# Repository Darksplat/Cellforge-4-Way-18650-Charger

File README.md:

# CellForge – 4 Way 18650 Charger & Analytics Platform

CellForge is an open hardware and software project for testing, analysing, and cataloguing 18650 lithium-ion cells.

It is inspired by Brett Watt’s original ASCD Nano charger and extends the concept with modern hardware, Wi-Fi connectivity, and a web-based analytics platform.

This repository contains **firmware, hardware, documentation, and web platform components** required to build and operate a connected 4-bay charger.

---

## Project Components

### Hardware
- 4-slot 18650 charger / discharger
- TP5100 charge controllers per slot
- Dual ADS1115 (16-bit I²C ADCs)
  - Battery voltage sensing
  - Load / discharge voltage sensing
- DS18B20 temperature sensors
- Active cooling with PWM fan control
- 3.3 V logic throughout (ESP32-safe)

### Firmware
- Target: **Arduino Nano ESP32 (ESP32-S3)**
- Wi-Fi connectivity
- Server heartbeat (PING) protocol
- RSSI (signal strength) reporting
- Internal resistance measurement
- Capacity and energy calculation
- Modular PlatformIO-based build

### Web Platform
- PHP + MySQL backend
- User authentication
- Charger registration and claiming
- Live charger connectivity status
- Signal strength visualisation
- Cell inventory
- Run ingestion (start, IR, complete, error)
- Cron-based offline detection

### Data
- Cell metadata (barcode-centric)
- Internal resistance results
- Capacity (mAh) and energy (Wh)
- Charger telemetry (presence, RSSI)

---

## Current Status

- Firmware: **Stable, Wi-Fi enabled**
- Connectivity: **Server-authoritative heartbeat**
- Telemetry: **RSSI reporting live**
- Offline detection: **Cron-enforced**
- UI: **Live status, signal bars, local time rendering**

---

## Repository Structure (high-level)

---

## Design Principles

- Server decides truth (presence, offline state)
- Firmware reports facts, not assumptions
- Browser renders user-local time
- Hardware remains Brett-compatible where practical
- Electrical safety first (3.3 V logic, no mixed-voltage traps)

---

## Licensing

Original ASCD Nano work:
- © Brett Watt
- Creative Commons BY-NC-SA 3.0

CellForge modifications:
- © Jeremy Younger
- Released under the same license unless otherwise stated

---

## Disclaimer

This project involves lithium-ion cells.
Improper use can result in fire, injury, or property damage.

You are responsible for ensuring safe construction, operation, and supervision.

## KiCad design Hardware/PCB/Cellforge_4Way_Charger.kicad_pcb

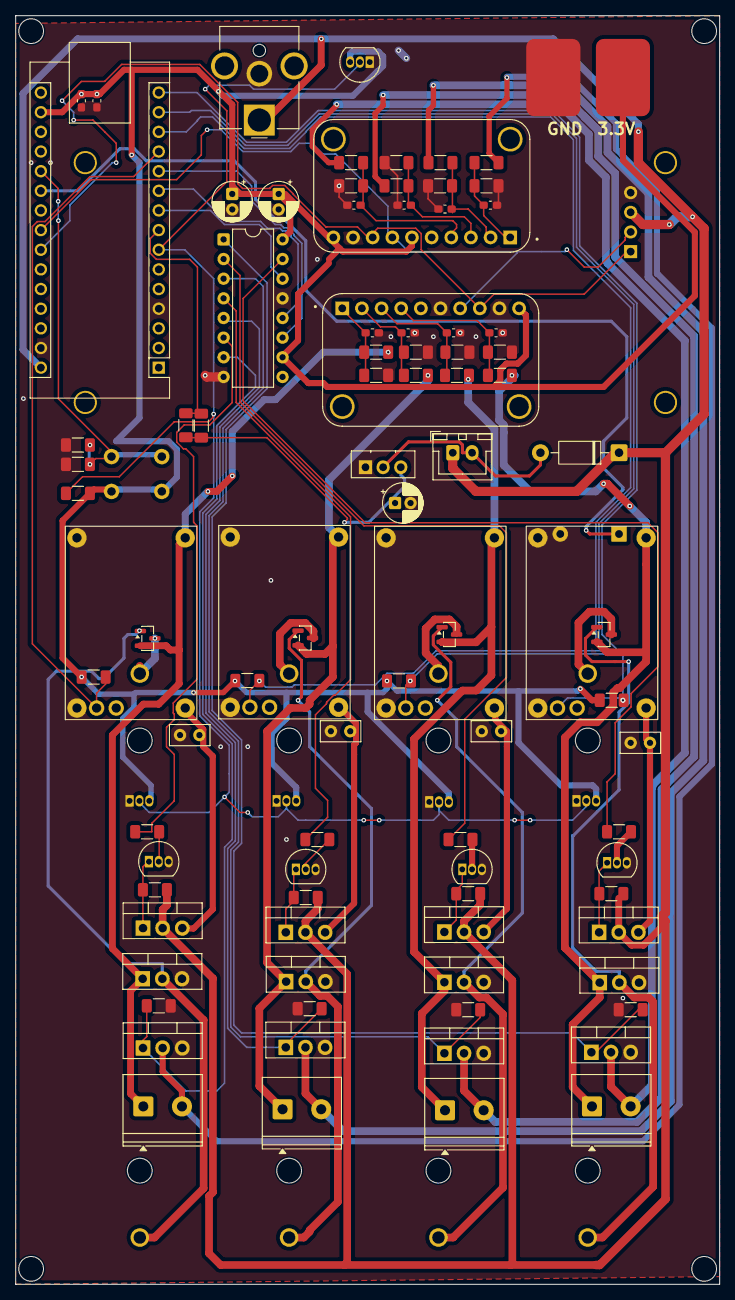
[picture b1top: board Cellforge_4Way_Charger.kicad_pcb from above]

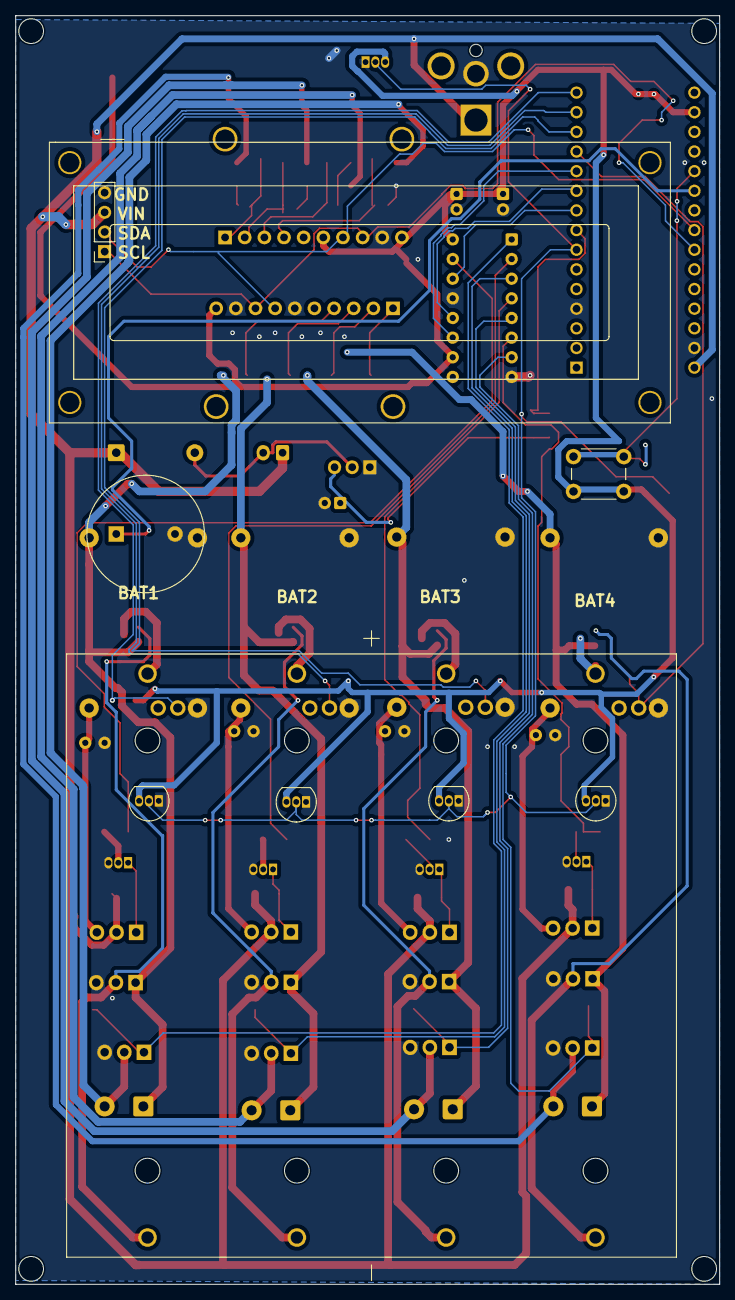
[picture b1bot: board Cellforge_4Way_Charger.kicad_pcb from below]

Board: 2 copper layers, 91.0 x 164.0 mm, 100 parts (8 on the bottom side), 62 nets.

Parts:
A1: Arduino_Nano_ESP32; Arduino_Nano
BT1: BK-18650-PC8; BAT_BK-18650-PC8
BZ1: Buzzer; Buzzer_15x7.5RM7.6
C1, C2, C11: 100uF; CP_Radial_D5.0mm_P2.00mm
C3, C4, C5, C6, C7, C8, C9, C10, C13: 100nF; C_0603_1608Metric_Pad1.08x0.95mm_HandSolder
C12, C16, C17, C18: C; C_Disc_D5.0mm_W2.5mm_P2.50mm
C14: 10nF; C_0603_1608Metric_Pad1.08x0.95mm_HandSolder
D1: 1N4007; D_DO-41_SOD81_P10.16mm_Horizontal
J1: Jack-DC; BarrelJack_CUI_PJ-063AH_Horizontal_CircularHoles
J2: Conn_01x02_MountingPin; JST_XH_B2B-XH-A_1x02_P2.50mm_Vertical
J3, J4, J6, J7: Screw_Terminal_01x02; TerminalBlock_Phoenix_PT-1,5-2-5.0-H_1x02_P5.00mm_Horizontal
J5: Conn_01x04_Socket; PinSocket_1x04_P2.54mm_Vertical
J8: Conn_01x02_Pin; PADS
Q1: BD139; TO-126-3_Vertical
Q2, Q3, Q8, Q23: AO3401A; SOT-23
Q6, Q7, Q9, Q10: BC547; TO-92_Inline
Q11, Q12, Q13, Q14, Q15, Q16, Q17, Q19: IRLZ44N; TO-220-3_Vertical
Q18, Q20, Q21, Q22: FQP27P06; TO-220-3_Vertical
R1, R21, R32, R36: 4.7K; R_1206_3216Metric_Pad1.30x1.75mm_HandSolder
R2, R3, R20, R35, R43, R50: 10K; R_1206_3216Metric_Pad1.30x1.75mm_HandSolder
R4, R5, R6, R7, R8, R9, R10, R11, R12, R13, R14, R15, R16, R17, R18, R19: 100K; R_1206_3216Metric_Pad1.30x1.75mm_HandSolder
R22: 1K; R_1206_3216Metric_Pad1.30x1.75mm_HandSolder
R23: 1k; R_1206_3216Metric_Pad1.30x1.75mm_HandSolder
R33, R34, R37, R38, R39, R40, R41, R42, R44: 470R; R_1206_3216Metric_Pad1.30x1.75mm_HandSolder
SW1: SW_Push; SW_PUSH_6mm
TP5100_Module1, TP5100_Module2, TP5100_Module3, TP5100_Module4: Untitled
U1, U2, U3, U4, U7: DS18B20; TO-92_Inline
U5: 74HC595; DIP-16_W7.62mm
U6, U9: ZC261500; MODULE_ZC261500

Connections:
+3.3V: A1.17 (3V3), C1.1, C2.1, C13.1, C14.1, J8.1, R1.1, R20.1, R35.1, R43.1, R50.1, SW1.2, U1.3 (V_{DD}), U2.3 (V_{DD}), U3.3 (V_{DD}), U4.3 (V_{DD}), U5.10 (~SRCLR), U5.16 (VCC), U6.6 (ADDR), U6.10 (VDD), U7.3 (V_{DD}), U9.10 (VDD)
+BAT1: J3.1, Q8.2 (S), Q15.1 (G), R4.1, TP5100_Module1.3 (BAT+)
+BAT2: J7.1, Q17.1 (G), Q23.2 (S), R12.1, TP5100_Module2.3 (BAT+)
+BAT3: J4.1, Q2.2 (S), Q12.1 (G), R18.1, TP5100_Module3.3 (BAT+)
+BAT4: J6.1, Q3.2 (S), Q19.1 (G), R16.1, TP5100_Module4.3 (BAT+)
-BAT1: BT1.4-, Q8.1 (G), Q15.2 (D)
-BAT2: BT1.3-, Q17.2 (D), Q23.1 (G)
-BAT3: BT1.2-, Q2.1 (G), Q12.2 (D)
-BAT4: BT1.1-, Q3.1 (G), Q19.2 (D)
BTN: A1.20 (A1), R2.2, R3.1, SW1.1
BUZZ: A1.21 (A2), BZ1.1 (+)
CD1: A1.15 (D12/CIPO), R20.2, TP5100_Module1.5 (CHRG)
CD2: A1.14 (D11/COPI), R43.2, TP5100_Module2.5 (CHRG)
CD3: A1.13 (D10/CS), R50.2, TP5100_Module3.5 (CHRG)
CD4: A1.12 (D9), R35.2, TP5100_Module4.5 (CHRG)
CEFT2: R42.2, U5.2 (QC)
CEFT3: R44.2, U5.4 (QE)
CEFT4: R34.2, U5.6 (QG)
CFET1: R38.2, U5.15 (QA)
DFET1: Q13.1 (G), R21.1, U5.1 (QB)
DFET2: Q16.1 (G), R36.1, U5.3 (QD)
DFET3: Q11.1 (G), R32.1, U5.5 (QF)
DFET4: Q14.1 (G), R33.1, U5.7 (QH)
DS: A1.9 (D6), U5.14 (SER)
FAN: A1.8 (D5), R22.1, R23.1
GND: A1.4 (GND), A1.29 (GND), BZ1.2 (-), C1.2, C2.2, C3.2, C4.2, C5.2, C6.2, C7.2, C8.2, C9.2, C10.2, C11.2, C12.2, C13.2, C14.2, C16.2, C17.2, C18.2, J1.2, J5.4, J8.2, Q1.1 (E), Q6.3 (E), Q7.3 (E), Q9.3 (E), Q10.3 (E), Q11.3 (S), Q12.3 (S), Q13.3 (S), Q14.3 (S), Q15.3 (S), Q16.3 (S), Q17.3 (S), Q19.3 (S), R2.1, R3.2, R6.2, R9.2, R11.2, R13.2, R14.2, R15.2, R17.2, R19.2, R21.2, R32.2, R33.2, R36.2, TP5100_Module1.2 (IN-), TP5100_Module1.4 (BAT-), TP5100_Module2.2 (IN-), TP5100_Module2.4 (BAT-), TP5100_Module3.2 (IN-), TP5100_Module3.4 (BAT-), TP5100_Module4.2 (IN-), TP5100_Module4.4 (BAT-), U1.1 (GND), U2.1 (GND), U3.1 (GND), U4.1 (GND), U5.8 (GND), U5.13 (~OE), U6.9 (GND), U7.1 (GND), U9.6 (ADDR), U9.9 (GND)
unnamed: D1.2 (A), J2.2, Q1.2 (C)
unnamed: C11.1, Q1.3 (B), R22.2, R23.2
unnamed: BT1.2+, Q2.3 (D)
unnamed: BT1.1+, Q3.3 (D)
unnamed: Q6.2 (B), R44.1
unnamed: Q7.2 (B), R38.1
unnamed: BT1.4+, Q8.3 (D)
unnamed: Q9.2 (B), R42.1
unnamed: Q10.2 (B), R34.1
unnamed: Q10.1 (C), Q21.1 (G), R40.2
unnamed: Q7.1 (C), Q18.1 (G), R39.2
unnamed: C12.1, Q18.3 (S), TP5100_Module1.1 (IN+)
unnamed: Q6.1 (C), Q20.1 (G), R37.2
unnamed: C17.1, Q20.3 (S), TP5100_Module3.1 (IN+)
unnamed: C18.1, Q21.3 (S), TP5100_Module4.1 (IN+)
unnamed: Q9.1 (C), Q22.1 (G), R41.1
unnamed: C16.1, Q22.3 (S), TP5100_Module2.1 (IN+)
unnamed: BT1.3+, Q23.3 (D)
unnamed: C4.1, R8.2, R9.1, U6.4 (A0)
unnamed: C6.1, R10.2, R11.1, U6.3 (A1)
unnamed: C8.1, R7.2, R15.1, U6.2 (A2)
unnamed: C7.1, R5.2, R6.1, U6.1 (A3)
unnamed: C3.1, R4.2, R14.1, U9.4 (A0)
unnamed: C5.1, R12.2, R13.1, U9.3 (A1)
unnamed: C10.1, R18.2, R19.1, U9.2 (A2)
unnamed: C9.1, R16.2, R17.1, U9.1 (A3)
RV1: J3.2, Q13.2 (D), R8.1
RV2: J7.2, Q16.2 (D), R10.1
RV3: J4.2, Q11.2 (D), R7.1
RV4: J6.2, Q14.2 (D), R5.1
SCL: A1.24 (SCL/A5), J5.1, U6.8 (SCL), U9.8 (SCL)
SDA: A1.23 (SDA/A4), J5.2, U6.7 (SDA), U9.7 (SDA)
SH/CP: A1.11 (D8), U5.11 (SRCLK)
ST/CP: A1.10 (D7), U5.12 (RCLK)
TMP: A1.7 (D4), R1.2, U1.2 (DQ), U2.2 (DQ), U3.2 (DQ), U4.2 (DQ), U7.2 (DQ)
VIn: A1.30 (VIN), D1.1 (K), J1.1, J2.1, J5.3, Q18.2 (D), Q20.2 (D), Q21.2 (D), Q22.2 (D), R37.1, R39.1, R40.1, R41.2

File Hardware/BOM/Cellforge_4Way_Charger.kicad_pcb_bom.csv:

Designator,Quantity,Value,Footprint,Package,MPN,DNP,Mount_Type,Description,MF,MAXIMUM_PACKAGE_HEIGHT,Price,Check_prices,STANDARD,PARTREV,SnapEDA_Link,MP,Description_1,Availability,MANUFACTURER,Sim.Device,Sim.Pins
A1,1,Arduino_Nano_ESP32,Arduino_Nano,,,,tht,"Arduino Nano board based on the ESP32-S3 with a dual-core 240 MHz processor, 384 kB ROM, 512 kB SRAM. Operates at 3.3V, with 5V USB-C® input and 6-21V VIN. Features Wi-Fi®, Bluetooth® LE, digital and analog pins, and supports SPI, I2C, UART, I2S, and CAN.",,,,,,,,,,,,,
BT1,1,BK-18650-PC8,BAT_BK-18650-PC8,None,,,tht,,MPD,21.54 mm,None,https://www.snapeda.com/parts/BK-18650-PC8/MPD/view-part/?ref=eda,Manufacturer Recommendations,L,https://www.snapeda.com/parts/BK-18650-PC8/MPD/view-part/?ref=snap,BK-18650-PC8,Battery Holder (Open) 18650 4 Cell PC Pin,In Stock,MPD,,
BZ1,1,Buzzer,Buzzer_15x7.5RM7.6,,,,tht,"Buzzer, polarized",,,,,,,,,,,,,
"C1, C11, C2",3,100uF,CP_Radial_D5.0mm_P2.00mm,,,,tht,Polarized capacitor,,,,,,,,,,,,,
"C10, C13, C3, C4, C5, C6, C7, C8, C9",9,100nF,C_0603_1608Metric_Pad1.08x0.95mm_HandSolder,,,,smt,Unpolarized capacitor,,,,,,,,,,,,,
"C12, C16, C17, C18",4,C,C_Disc_D5.0mm_W2.5mm_P2.50mm,,,,tht,Unpolarized capacitor,,,,,,,,,,,,,
C14,1,10nF,C_0603_1608Metric_Pad1.08x0.95mm_HandSolder,,,,smt,Unpolarized capacitor,,,,,,,,,,,,,
D1,1,1N4007,D_DO-41_SOD81_P10.16mm_Horizontal,,,,tht,"1000V 1A General Purpose Rectifier Diode, DO-41",,,,,,,,,,,,D,1=K 2=A
J1,1,Jack-DC,BarrelJack_CUI_PJ-063AH_Horizontal_CircularHoles,,,,tht,DC Barrel Jack,,,,,,,,,,,,,
J2,1,Conn_01x02_MountingPin,JST_XH_B2B-XH-A_1x02_P2.50mm_Vertical,,,,tht,"Generic connectable mounting pin connector, single row, 01x02, script generated (kicad-library-utils/schlib/autogen/connector/)",,,,,,,,,,,,,
"J3, J4, J6, J7",4,Screw_Terminal_01x02,"TerminalBlock_Phoenix_PT-1,5-2-5.0-H_1x02_P5.00mm_Horizontal",,,,tht,"Generic screw terminal, single row, 01x02, script generated (kicad-library-utils/schlib/autogen/connector/)",,,,,,,,,,,,,
J5,1,Conn_01x04_Socket,PinSocket_1x04_P2.54mm_Vertical,,,,tht,"Generic connector, single row, 01x04, script generated",,,,,,,,,,,,,
J8,1,Conn_01x02_Pin,PADS,,,,smt,"Generic connector, single row, 01x02, script generated",,,,,,,,,,,,,
Q1,1,BD139,TO-126-3_Vertical,,,,tht,"1.5A Ic, 80V Vce, Low Voltage Transistor, TO-126",,,,,,,,,,,,,
"Q10, Q6, Q7, Q9",4,BC547,TO-92_Inline,,,,tht,"0.1A Ic, 45V Vce, Small Signal NPN Transistor, TO-92",,,,,,,,,,,,,
"Q11, Q12, Q13, Q14, Q15, Q16, Q17, Q19",8,IRLZ44N,TO-220-3_Vertical,,,,tht,"47A Id, 55V Vds, 22mOhm Rds Single N-Channel HEXFET Power MOSFET, TO-220AB",,,,,,,,,,,,,
"Q18, Q20, Q21, Q22",4,FQP27P06,TO-220-3_Vertical,,,,tht,"-27A Id, -60V Vds, QFET P-Channel MOSFET, TO-220",,,,,,,,,,,,,
"Q2, Q23, Q3, Q8",4,AO3401A,SOT-23,,,,smt,"-4.0A Id, -30V Vds, P-Channel MOSFET, SOT-23",,,,,,,,,,,,,
"R1, R21, R32, R36",4,4.7K,R_1206_3216Metric_Pad1.30x1.75mm_HandSolder,,,,smt,Resistor,,,,,,,,,,,,,
"R10, R11, R12, R13, R14, R15, R16, R17, R18, R19, R4, R5, R6, R7, R8, R9",16,100K,R_1206_3216Metric_Pad1.30x1.75mm_HandSolder,,,,smt,Resistor,,,,,,,,,,,,,
"R2, R20, R3, R35, R43, R50",6,10K,R_1206_3216Metric_Pad1.30x1.75mm_HandSolder,,,,smt,Resistor,,,,,,,,,,,,,
R22,1,1K,R_1206_3216Metric_Pad1.30x1.75mm_HandSolder,,,,smt,Resistor,,,,,,,,,,,,,
R23,1,1k,R_1206_3216Metric_Pad1.30x1.75mm_HandSolder,,,,smt,Resistor,,,,,,,,,,,,,
"R33, R34, R37, R38, R39, R40, R41, R42, R44",9,470R,R_1206_3216Metric_Pad1.30x1.75mm_HandSolder,,,,smt,Resistor,,,,,,,,,,,,,
SW1,1,SW_Push,SW_PUSH_6mm,,,,tht,"Push button switch, generic, two pins",,,,,,,,,,,,,
"TP5100_Module1, TP5100_Module2, TP5100_Module3, TP5100_Module4",4,~,Untitled,,,,tht,,,,,,,,,,,,,,
"U1, U2, U3, U4, U7",5,DS18B20,TO-92_Inline,,,,tht,Programmable Resolution 1-Wire Digital Thermometer TO-92,,,,,,,,,,,,,
U5,1,74HC595,DIP-16_W7.62mm,,,,tht,8-bit serial in/out Shift Register 3-State Outputs,,,,,,,,,,,,,
"U6, U9",2,ZC261500,MODULE_ZC261500,None,,,tht,,YKS,NA,None,https://www.snapeda.com/parts/ZC261500/YKS/view-part/?ref=eda,Manufacturer Recommendations,NA,https://www.snapeda.com/parts/ZC261500/YKS/view-part/?ref=snap,ZC261500,ADS1115 Module ADC 4 channel with Pro Gain Amplifier for Arduino RPi,Not in stock,YKS,,

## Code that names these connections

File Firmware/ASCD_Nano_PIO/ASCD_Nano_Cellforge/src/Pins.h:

#pragma once

// =====================================================
// Pins.h
// Central pin definitions for ASCD Nano ESP32
// Hardware: Arduino Nano ESP32
// Schematic: Rev 2.0 (ADS1115, no analog mux)
// =====================================================

// =====================================================
// ESP32 Fan PWM (LEDC)
// =====================================================
#define FAN_PWM_CHANNEL   0
#define FAN_PWM_FREQ      25000   // 25 kHz (quiet fan)
#define FAN_PWM_RES       8        // 8-bit resolution

// ----------------------
// I2C (shared bus)
// ----------------------
static const uint8_t PIN_SDA = A4;
static const uint8_t PIN_SCL = A5;


// ----------------------
// 74HC595 Shift Register
// ----------------------
static const uint8_t PIN_SR_DATA = D6;   // DS
static const uint8_t PIN_SR_LATCH = D7;  // ST/CP
static const uint8_t PIN_SR_CLOCK = D8;  // SH/CP


// ----------------------
// TP5100 Charge Status Inputs
// (one per slot, no mux)
// ----------------------
static const uint8_t PIN_CD1 = D12;
static const uint8_t PIN_CD2 = D11;
static const uint8_t PIN_CD3 = D10;
static const uint8_t PIN_CD4 = D9;


// ----------------------
// Fan + Temperature
// ----------------------
static const uint8_t PIN_FAN = D5;   // PWM fan control
static const uint8_t PIN_TMP = D4;   // OneWire temperature bus


// ----------------------
// Button + Buzzer
// ----------------------
static const uint8_t PIN_BTN  = A1;
static const uint8_t PIN_BUZZ = A2;


// ----------------------
// ADS1115 I2C Addresses
// ----------------------
// Battery voltages ADS1115 (ADDR = GND)
static const uint8_t ADS_BAT_ADDR = 0x48;

// Load voltages ADS1115 (ADDR = 3V3)
static const uint8_t ADS_LOAD_ADDR = 0x49;


// ----------------------
// ADS1115 Channel Mapping
// ----------------------
// Battery voltages
static const uint8_t ADS_BV1 = 0; // AIN0
static const uint8_t ADS_BV2 = 1; // AIN1
static const uint8_t ADS_BV3 = 2; // AIN2
static const uint8_t ADS_BV4 = 3; // AIN3

// Load voltages
static const uint8_t ADS_RV1 = 0; // AIN0
static const uint8_t ADS_RV2 = 1; // AIN1
static const uint8_t ADS_RV3 = 2; // AIN2
static const uint8_t ADS_RV4 = 3; // AIN3

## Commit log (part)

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2025-12-15 Update README with project details and guidelines
    Expanded project details, safety notices, repository structure, current status, getting started guide, contributing guidelines, license information, and credits.
2025-12-15 File Structure
2025-12-15 Add files
2025-12-15 import: legacy Arduino Nano 4x charger baseline and reference material
2025-12-15 Folder Structure
2025-12-15 Ver 0.1 New Nano Code
2025-12-15 Folder stucture
2025-12-15 docs: add MIT license for CellForge project
2025-12-15 docs: add contributing guidelines
2026-01-02 Add files via upload
    Schematic v2.0
2026-01-02 Add V2 schematic change summary for smart charger
    This document summarizes the schematic changes made in V2 of the Arduino 4× 18650 Smart Charger, detailing modifications to the microcontroller, measurement architecture, and pin mapping.
2026-01-02 Add ADS1115 Technical Note
    This technical note explains the rationale for selecting the ADS1115, its configuration in the V2 schematic, and how it enhances the design by replacing the analogue multiplexer used in the original 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
2026-01-02 Update changelog for ESP32 Nano hardware refactor
    Finalised migration to Arduino Nano ESP32 with new ADC architecture. Removed analogue multiplexer and standardised I²C bus.
2026-01-02 Update changelog for ESP32 Nano hardware refactor
    Finalised migration to Arduino Nano ESP32 with dual ADS1115 architecture. Updated power strategy and resolved mixed-voltage logic issues.
2026-01-12 Add initial features and roadmap for CellForge
2026-01-12 Revise CellForge roadmap with implementation details
    Updated the CellForge roadmap to include current implementation status, pending UI work, and planned features, while clarifying out-of-scope items.
2026-01-12 Revise CellForge roadmap with current and planned features
    Updated the roadmap to reflect the current implementation status and planned development for the CellForge project, including sections on hardware, firmware, website development, and documentation.
2026-01-12 Add changelog for project version history
    Document notable changes and version history for the project.
2026-01-12 Revise README for CellForge project details
    Updated project description, structure, and components for clarity and detail.
2026-01-12 Revise roadmap structure and content clarity
    Updated the roadmap to clarify sections and restructured content for better readability.
2026-01-12 Add ignore rule for CellForge website media
